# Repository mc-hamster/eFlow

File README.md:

# eFlow
ESP8266 Based Reflow Oven

For more information, go to: http://www.casler.org/wordpress/?p=124

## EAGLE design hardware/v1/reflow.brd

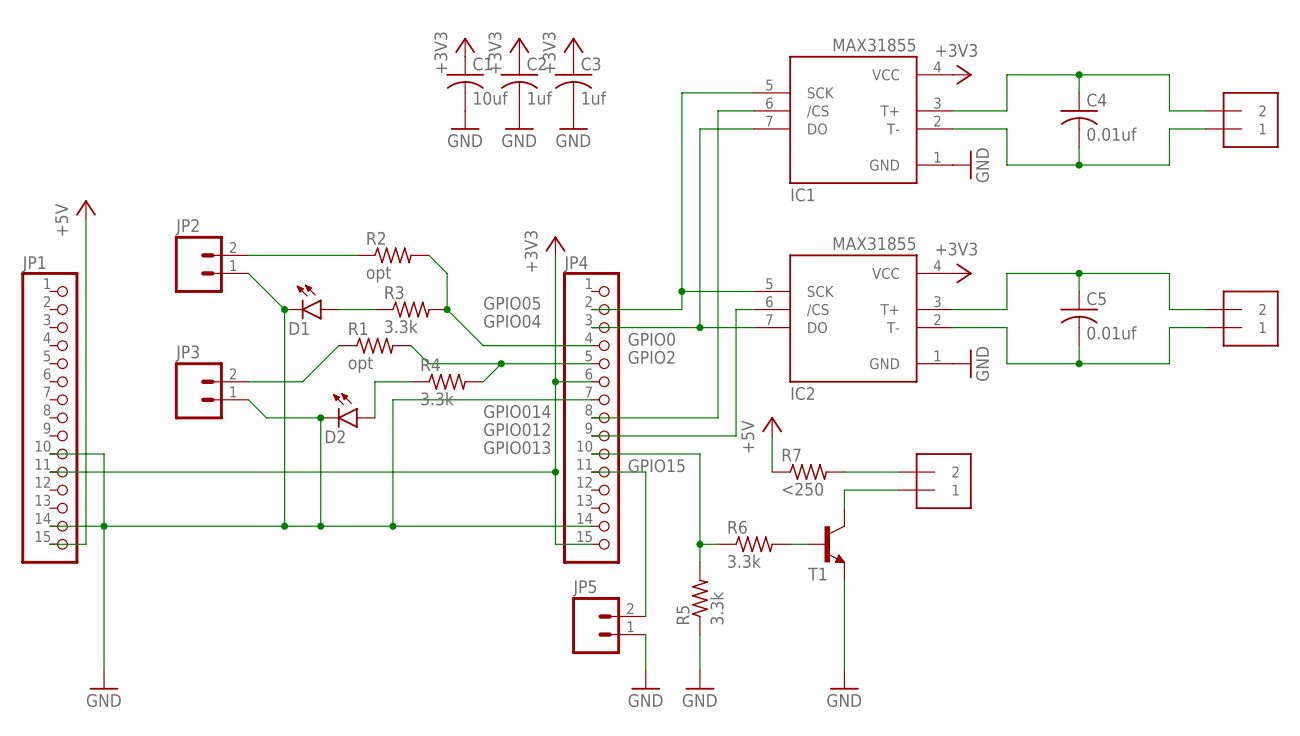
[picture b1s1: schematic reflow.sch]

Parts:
C1: 10uf; C0603
C2, C3: 1uf; C0603
C4, C5: 0.01uf; C0603
D1, D2: LED0603; LED-0603
IC1, IC2: MAX31855; SO08
J1, J2, J3: 1X2-3.5MM
JP1, JP4: PINHD-1X15; 1X15
JP2, JP3, JP5: M02PTH; 1X02
R1, R2: opt; R0603
R3, R4, R5, R6: 3.3k; R0603
R7: <250; R0603
T1: MMBT3904LT1-NPN-SOT23-BEC; SOT23-BEC; MPN MMBT2222A

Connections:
+3V3: C1.1, C2.1, C3.1, IC1.4 (VCC), IC2.4 (VCC), JP1.11, JP4.6, JP4.15
+5V: JP1.15, R7.1
GND: C1.2, C2.2, C3.2, D1.C, D2.C, IC1.1 (GND), IC2.1 (GND), JP1.10, JP1.14, JP2.1, JP3.1, JP4.7, JP4.14, JP5.1, R5.1, T1.E
unnamed: C5.2, IC2.2 (T-), J3.1
unnamed: C4.2, IC1.2 (T-), J2.1
unnamed: C4.1, IC1.3 (T+), J2.2
unnamed: IC1.5 (SCK), IC2.5 (SCK), JP4.2
unnamed: C5.1, IC2.3 (T+), J3.2
unnamed: IC1.7 (DO), IC2.7 (DO), JP4.3
unnamed: IC1.6 (/CS), JP4.8
unnamed: IC2.6 (/CS), JP4.9
unnamed: J1.2, R7.2
unnamed: J1.1, T1.C
unnamed: JP4.10, R5.2, R6.1
unnamed: JP2.2, R2.1
unnamed: D2.A, R4.1
unnamed: D1.A, R3.1
unnamed: JP3.2, R1.1
unnamed: JP4.11, JP5.2
unnamed: JP4.4, R2.2, R3.2
unnamed: JP4.5, R1.2, R4.2
unnamed: R6.2, T1.B

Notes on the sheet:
GPIO05
GPIO04
GPIO014
GPIO012
GPIO013
GPIO0
GPIO2
GPIO15

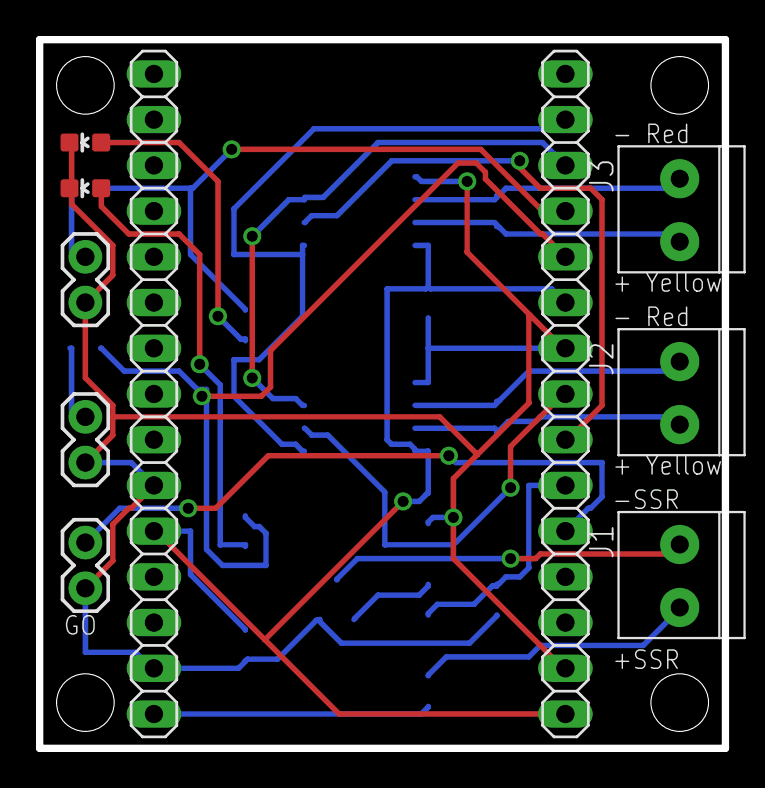
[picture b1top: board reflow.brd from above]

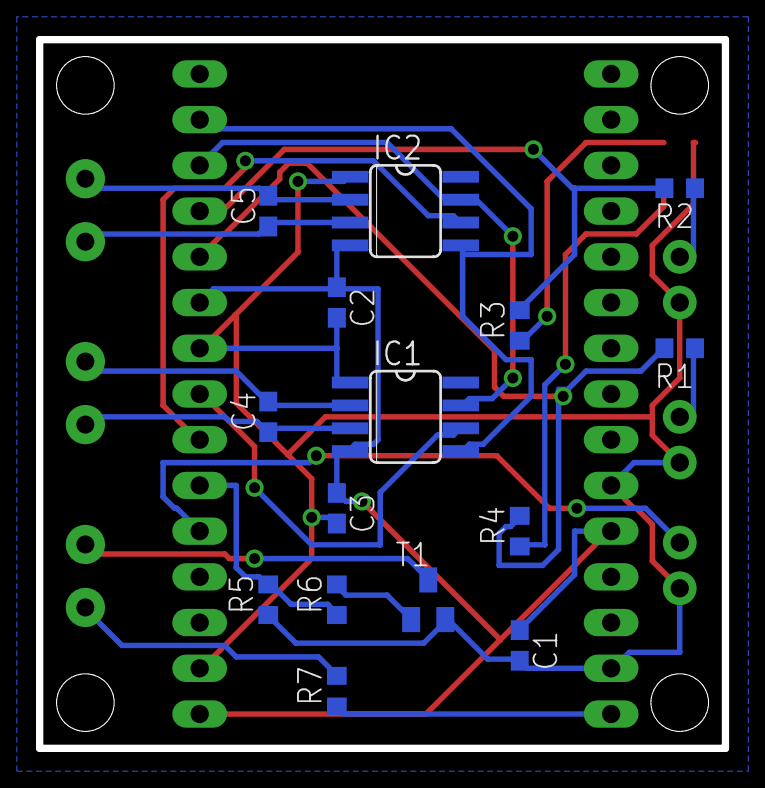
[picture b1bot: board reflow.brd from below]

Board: 2 copper layers, 38.1 x 39.4 mm, 25 parts (15 on the bottom side), 22 nets.

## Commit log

2016-05-07 Initial checkin of eFlow
2016-05-07 Initial Checkin
2016-05-07 eFlow Initial Checkin
2016-05-07 Added labels in schematic to terminal blocks.
2016-05-07 Moved strings into flash to save heap size. Will do this more later.
2016-05-09 If user_flash button is held down for 5 seconds after power on, yado will enter admin mode. This will let us configure IP settings.
2016-05-09 Removed unused comments
2016-05-09 Blink the CONNECTED led when in admin mode. Set CONNECTED led to constant when not in admin mode and connected to the AP.
2016-05-14 Getting ready to finish v0.0.1
2016-05-14 Commenting out profile selection from 0.0.1
2016-05-14 Adjusting time to restart.
2016-05-15 Initial check in of v0.0.2
2016-05-15 Implemented OTA through both Arduino UI and eflow.local/update
2016-05-15 There's a bug in the ArduinoOTA library where it overwrites the mdns responder. Removing support for ArduinoOTA for the time being.

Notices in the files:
parts and their libraries:
SparkFun-LED: Licensing: Creative Commons ShareAlike 4.0 International - https://creativecommons.org/licenses/by-sa/4.0
